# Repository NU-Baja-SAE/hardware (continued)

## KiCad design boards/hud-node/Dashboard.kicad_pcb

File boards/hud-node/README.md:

# hud-node

KiCad project for the HUD node board. Add `.kicad_pro`/`.kicad_sch`/`.kicad_pcb` files here, with generated fab outputs under `fab-outputs/` (gitignored).

<!-- CI trigger test -->

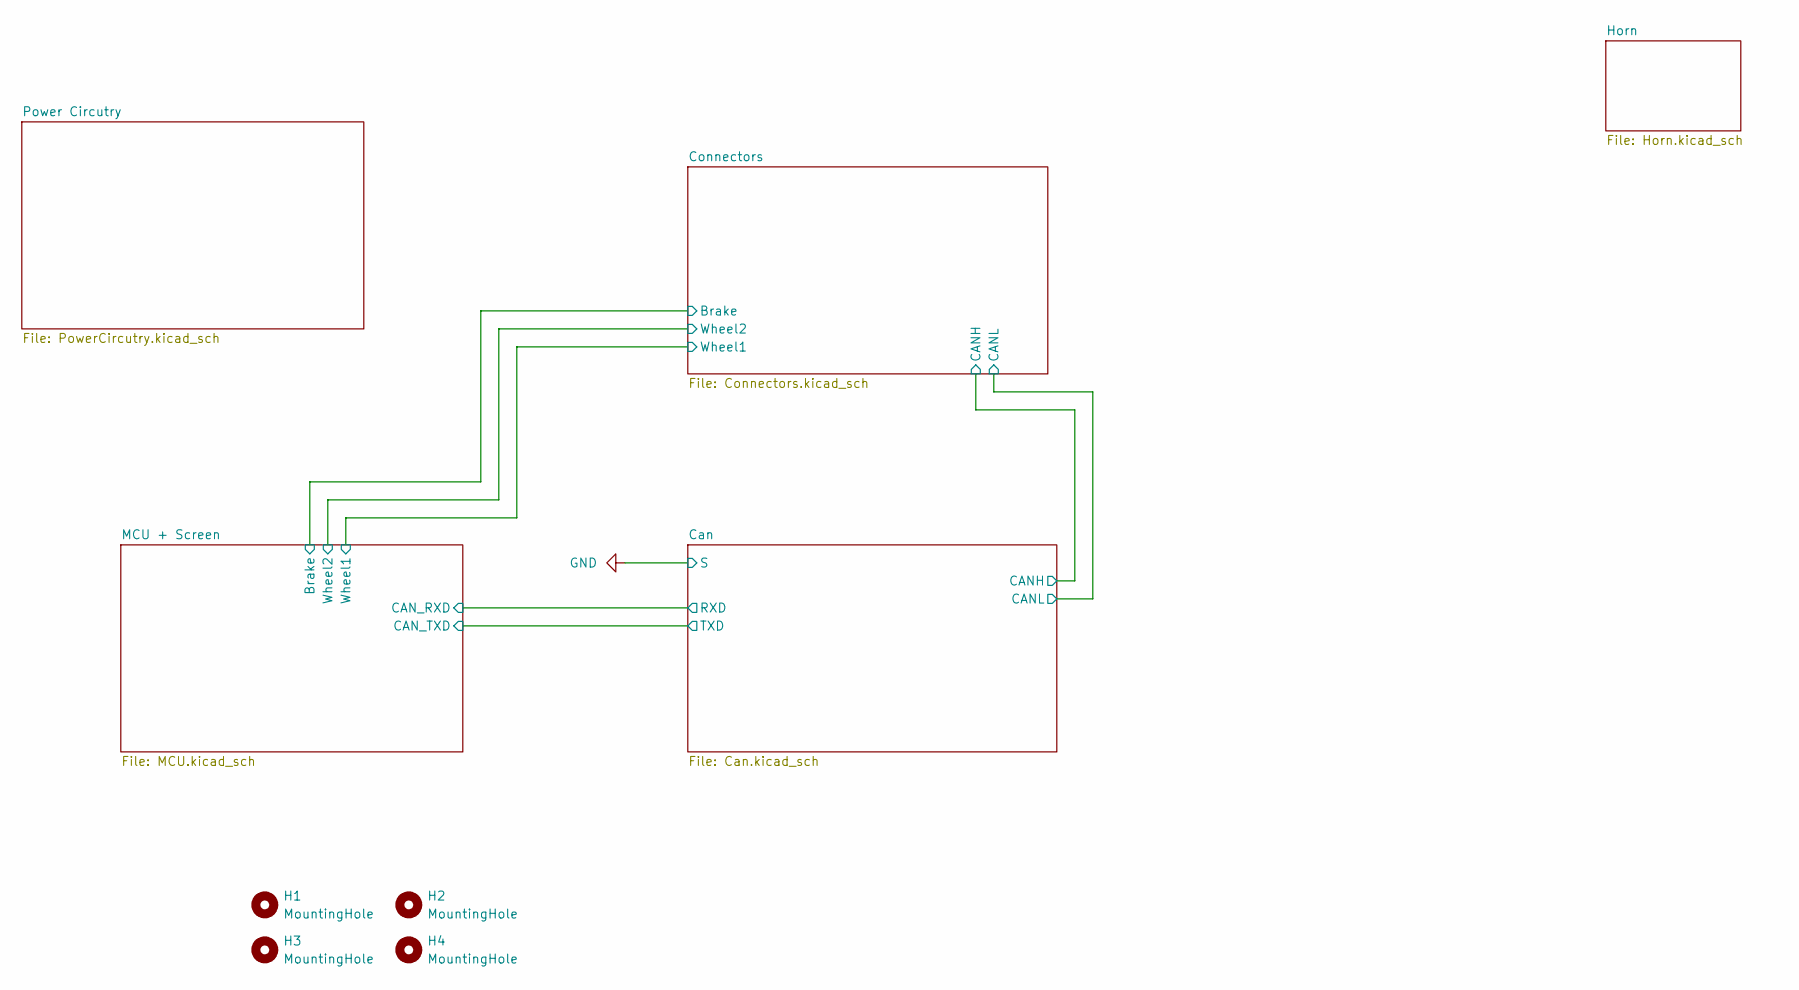
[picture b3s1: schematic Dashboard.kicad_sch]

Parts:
H1, H2, H3, H4: MountingHole; MountingHole_3.2mm_M3

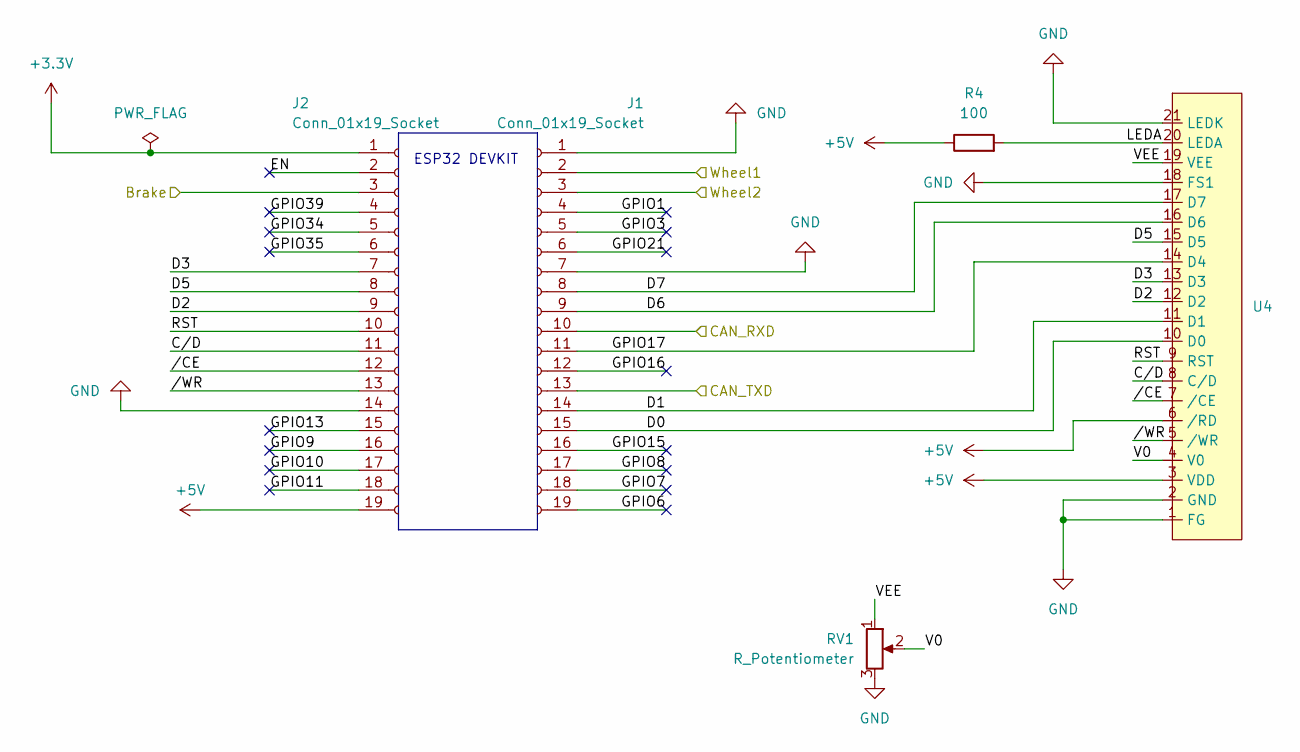
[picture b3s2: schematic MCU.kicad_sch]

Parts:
J1, J2: Conn_01x19_Socket; PinSocket_1x19_P2.54mm_Vertical
R4: 100; R_0603_1608Metric_Pad0.98x0.95mm_HandSolder
RV1: R_Potentiometer; Potentiometer_Bourns_3386F_Vertical
U4: PinHeader_1x21_P2.54mm_Vertical

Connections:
+3.3V: J2.1; also elsewhere on the board
+5V: J2.19, R4.1, U4.3 (VDD), U4.6 (/RD); also elsewhere on the board
/Can/RXD: J1.13; also elsewhere on the board
/Can/TXD: J1.10; also elsewhere on the board
/Connectors/Brake: J2.3; also elsewhere on the board
/Connectors/Wheel1: J1.2; also elsewhere on the board
/Connectors/Wheel2: J1.3; also elsewhere on the board
/MCU + Screen/C/D: J2.11, U4.8 (C/D)
/MCU + Screen/D0: J1.15, U4.10 (D0)
/MCU + Screen/D1: J1.14, U4.11 (D1)
/MCU + Screen/D3: J2.7, U4.13 (D3)
/MCU + Screen/D5: J2.8, U4.15 (D5)
/MCU + Screen/D6: J1.9, U4.16 (D6)
/MCU + Screen/D7: J1.8, U4.17 (D7)
/MCU + Screen/EN: J2.2
/MCU + Screen/GPIO1: J1.4
/MCU + Screen/GPIO3: J1.5
/MCU + Screen/GPIO6: J1.19
/MCU + Screen/GPIO7: J1.18
/MCU + Screen/GPIO8: J1.17
/MCU + Screen/GPIO9: J2.16
/MCU + Screen/GPIO10: J2.17
/MCU + Screen/GPIO11: J2.18
/MCU + Screen/GPIO13: J2.15
/MCU + Screen/GPIO15: J1.16
/MCU + Screen/GPIO16: J1.12
/MCU + Screen/GPIO17: J1.11, U4.14 (D4)
/MCU + Screen/GPIO21: J1.6
/MCU + Screen/GPIO34: J2.5
/MCU + Screen/GPIO39: J2.4
/MCU + Screen/LEDA: R4.2, U4.20 (LEDA)
/MCU + Screen/RST: J2.10, U4.9 (RST)
/MCU + Screen/V0: RV1.2, U4.4 (V0)
/MCU + Screen/VEE: RV1.1, U4.19 (VEE)
/MCU + Screen//CE: J2.12, U4.7 (/CE)
/MCU + Screen//WR: J2.13, U4.5 (/WR)
GND: J1.1, J1.7, J2.14, RV1.3, U4.1 (FG), U4.2 (GND), U4.18 (FS1), U4.21 (LEDK); also elsewhere on the board

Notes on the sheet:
ESP32 DEVKIT

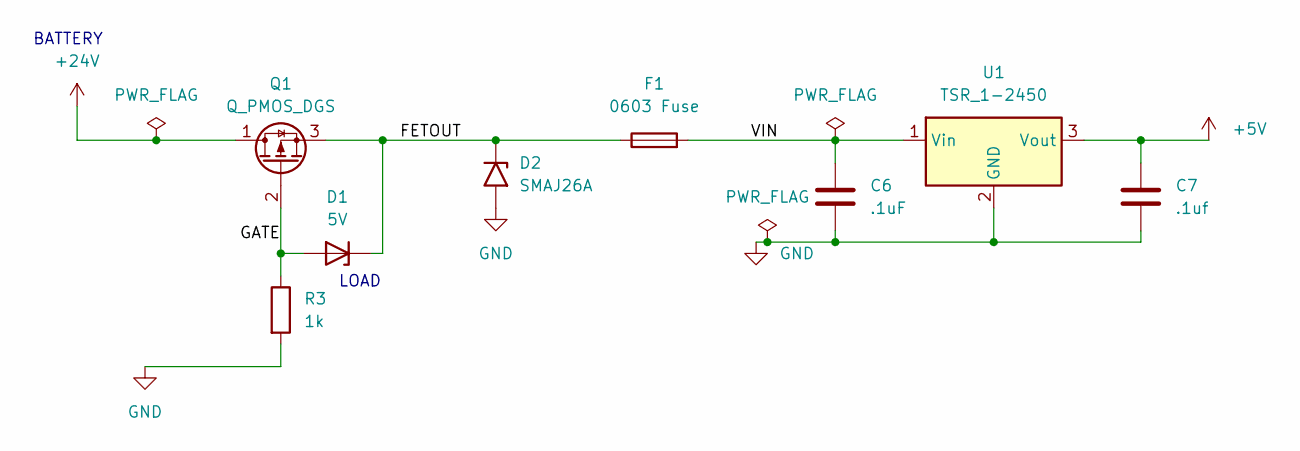
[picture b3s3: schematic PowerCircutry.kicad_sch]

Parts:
C6: .1uF; C_0603_1608Metric_Pad1.08x0.95mm_HandSolder
C7: .1uf; C_0805_2012Metric_Pad1.18x1.45mm_HandSolder
D1: 5V; D_SMA
D2: SMAJ26A; D_SMA
F1: 0603 Fuse; Fuse_0603_1608Metric_Pad1.05x0.95mm_HandSolder
Q1: Q_PMOS_DGS; SOT-23-3
R3: 1k; R_0603_1608Metric_Pad0.98x0.95mm_HandSolder
U1: TSR_1-2450; Converter_DCDC_TRACO_TSR-1_THT

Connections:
+5V: C7.1, U1.3 (Vout); also elsewhere on the board
+24V: Q1.1 (D); also elsewhere on the board
/Power Circutry/FETOUT: D1.1 (K), D2.1 (A1), F1.1, Q1.3 (S)
/Power Circutry/GATE: D1.2 (A), Q1.2 (G), R3.1
/Power Circutry/VIN: C6.1, F1.2, U1.1 (Vin)
GND: C6.2, C7.2, D2.2 (A2), R3.2, U1.2 (GND); also elsewhere on the board

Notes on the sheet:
LOAD
BATTERY

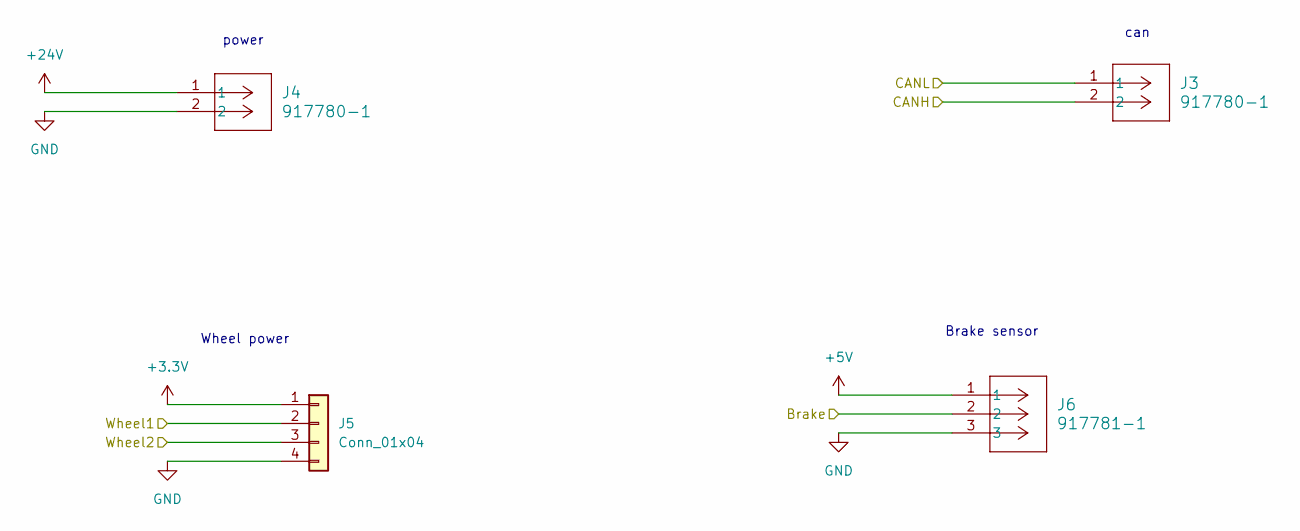
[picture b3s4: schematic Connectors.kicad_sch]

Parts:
J3, J4: 917780-1; TE-Connectivity_ 917780
J5: Conn_01x04; TE-Connectivity_917782
J6: 917781-1; TE-Connectivity_917781

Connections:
+3.3V: J5.1; also elsewhere on the board
+5V: J6.1; also elsewhere on the board
+24V: J4.1; also elsewhere on the board
/Can/CANH: J3.2; also elsewhere on the board
/Can/CANL: J3.1; also elsewhere on the board
/Connectors/Brake: J6.2; also elsewhere on the board
/Connectors/Wheel1: J5.2; also elsewhere on the board
/Connectors/Wheel2: J5.3; also elsewhere on the board
GND: J4.2, J5.4, J6.3; also elsewhere on the board

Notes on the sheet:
power
Brake sensor
Wheel power
can

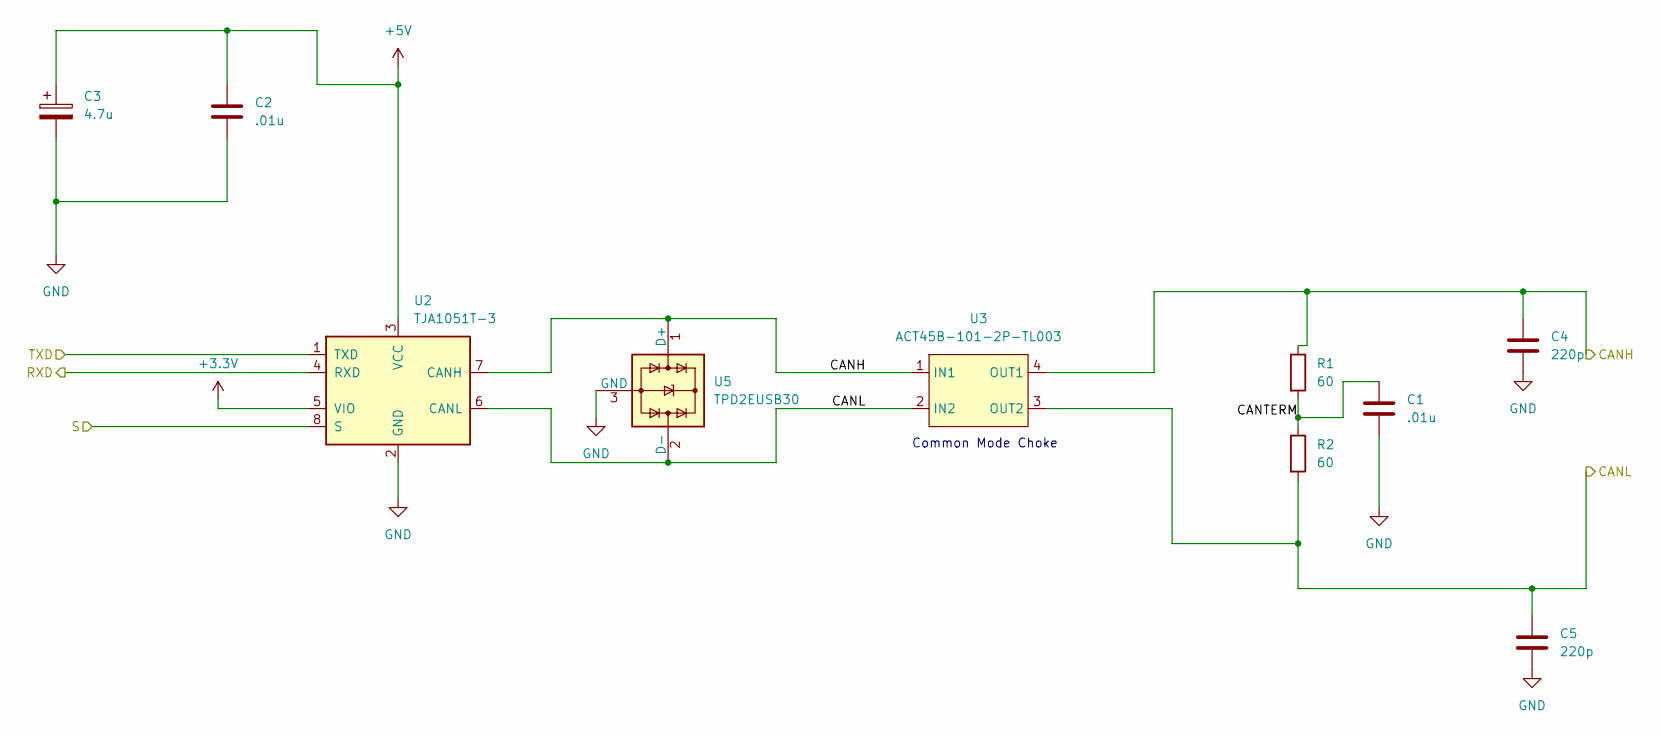
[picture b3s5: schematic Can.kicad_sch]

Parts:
C1, C2: .01u; C_0805_2012Metric_Pad1.18x1.45mm_HandSolder
C3: 4.7u; C_0603_1608Metric_Pad1.08x0.95mm_HandSolder
C4, C5: 220p; C_0603_1608Metric_Pad1.08x0.95mm_HandSolder
R1, R2: 60; R_1206_3216Metric_Pad1.30x1.75mm_HandSolder
U2: TJA1051T-3; SOIC-8_3.9x4.9mm_P1.27mm
U3: ACT45B-101-2P-TL003
U5: TPD2EUSB30; Texas_DRT-3

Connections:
+3.3V: U2.5 (VIO); also elsewhere on the board
+5V: C2.1, C3.1, U2.3 (VCC); also elsewhere on the board
/Can/CANH: C4.1, R1.1, U2.7 (CANH), U3.1 (IN1), U3.4 (OUT1), U5.1 (D+); also elsewhere on the board
/Can/CANL: C5.1, R2.2, U2.6 (CANL), U3.2 (IN2), U3.3 (OUT2), U5.2 (D-); also elsewhere on the board
/Can/CANTERM: C1.1, R1.2, R2.1
/Can/RXD: U2.4 (RXD); also elsewhere on the board
/Can/TXD: U2.1 (TXD); also elsewhere on the board
GND: C1.2, C2.2, C3.2, C4.2, C5.2, U2.2 (GND), U2.8 (S), U5.3 (GND); also elsewhere on the board

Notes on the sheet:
Common Mode Choke

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
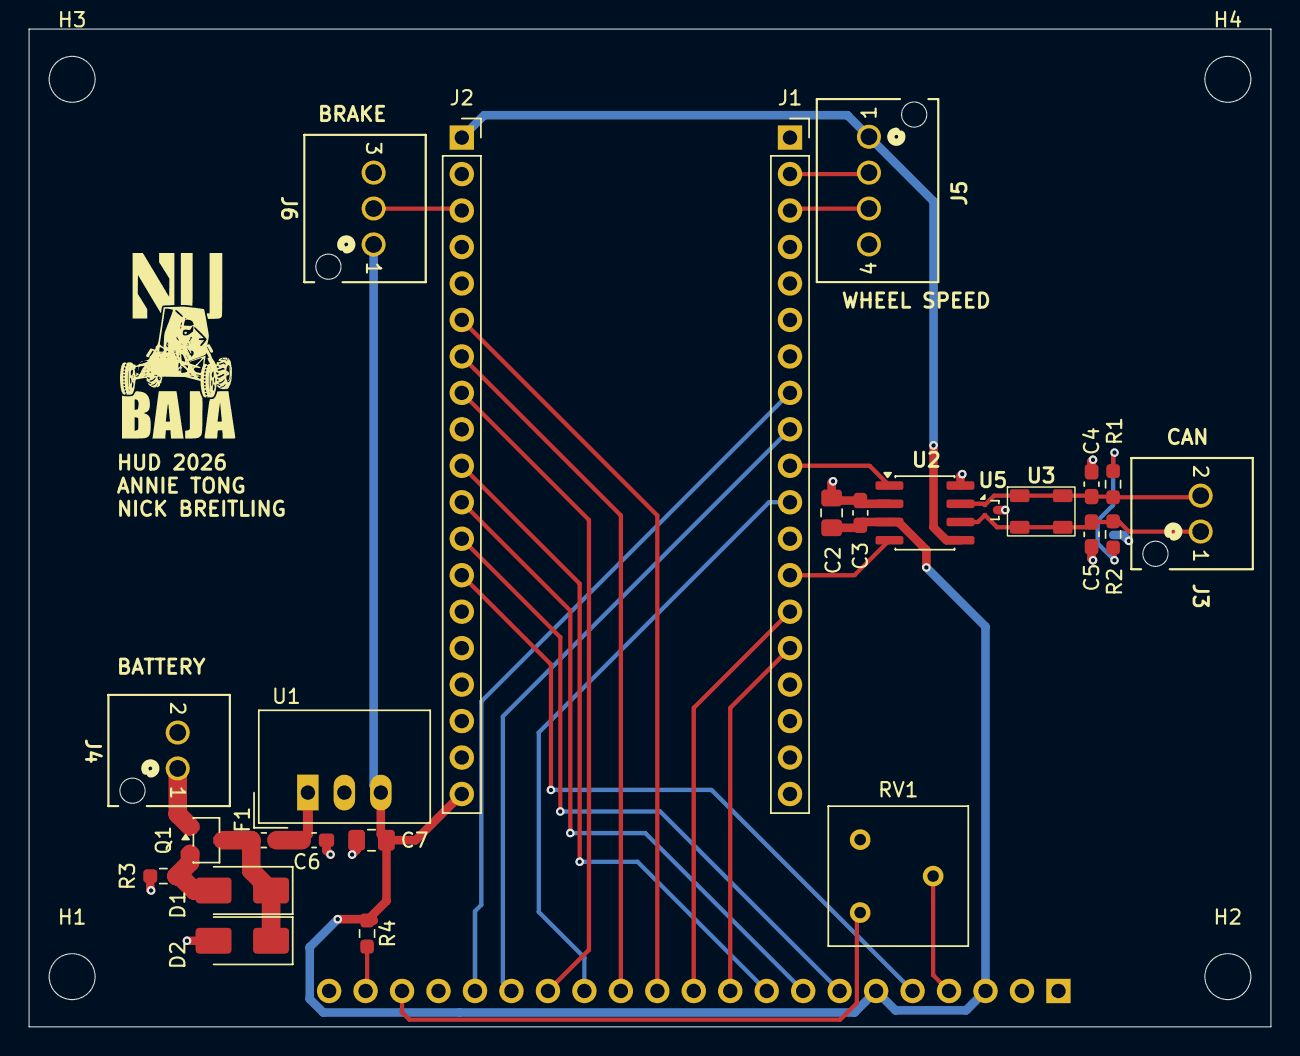
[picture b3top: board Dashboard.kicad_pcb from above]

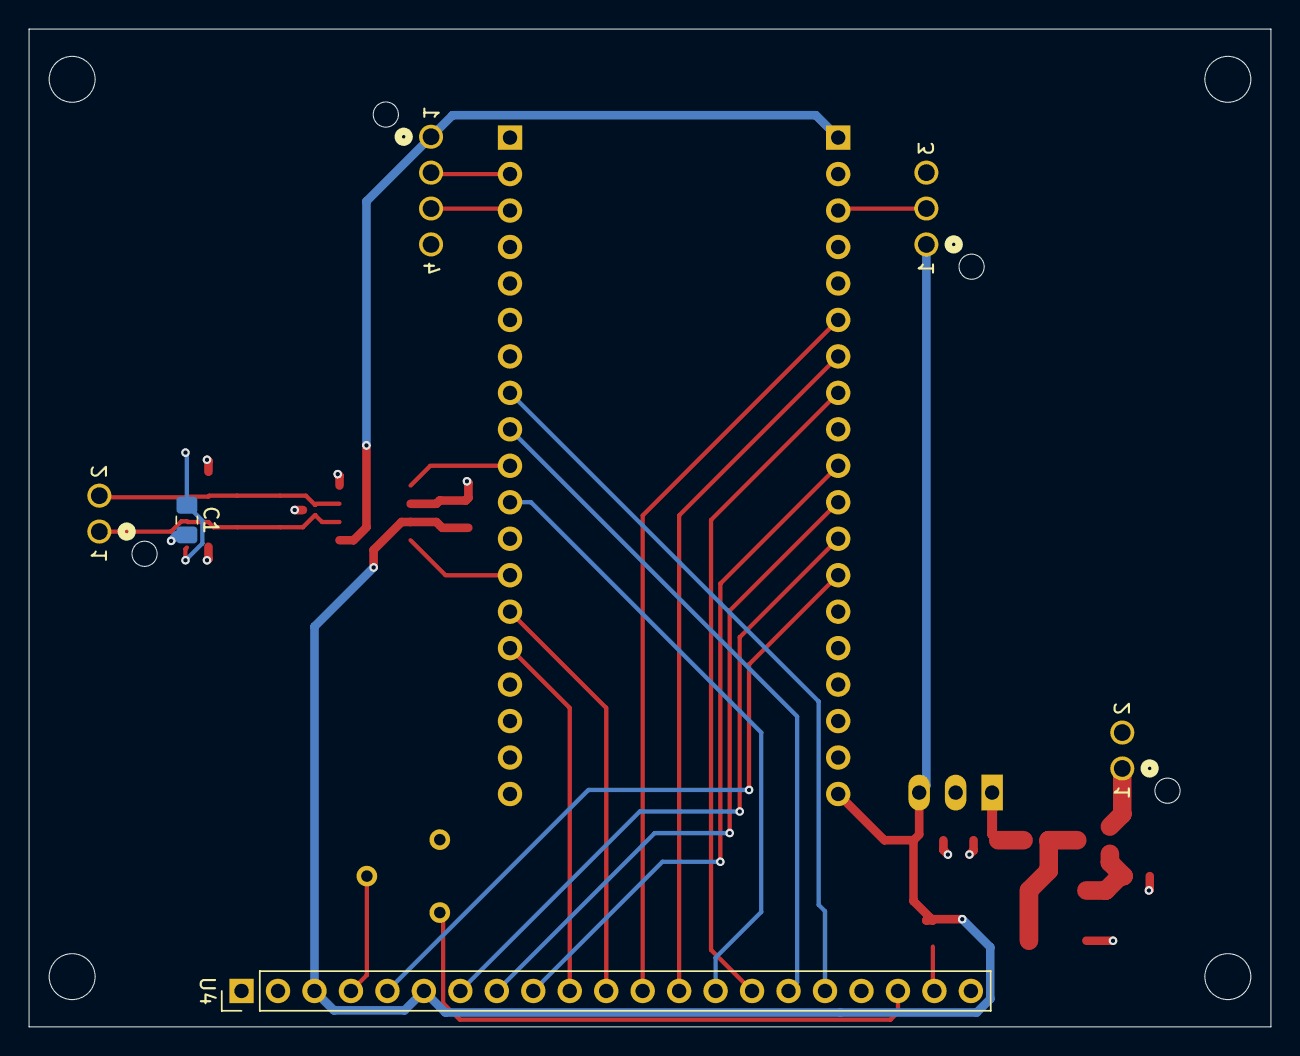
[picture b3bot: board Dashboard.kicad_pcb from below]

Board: 4 copper layers, 86.5 x 69.5 mm, 31 parts (2 on the bottom side), 30 nets.

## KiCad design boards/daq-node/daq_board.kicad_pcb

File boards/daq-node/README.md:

# daq-node

KiCad project for the DAQ node board. Add `.kicad_pro`/`.kicad_sch`/`.kicad_pcb` files here, with generated fab outputs under `fab-outputs/` (gitignored).

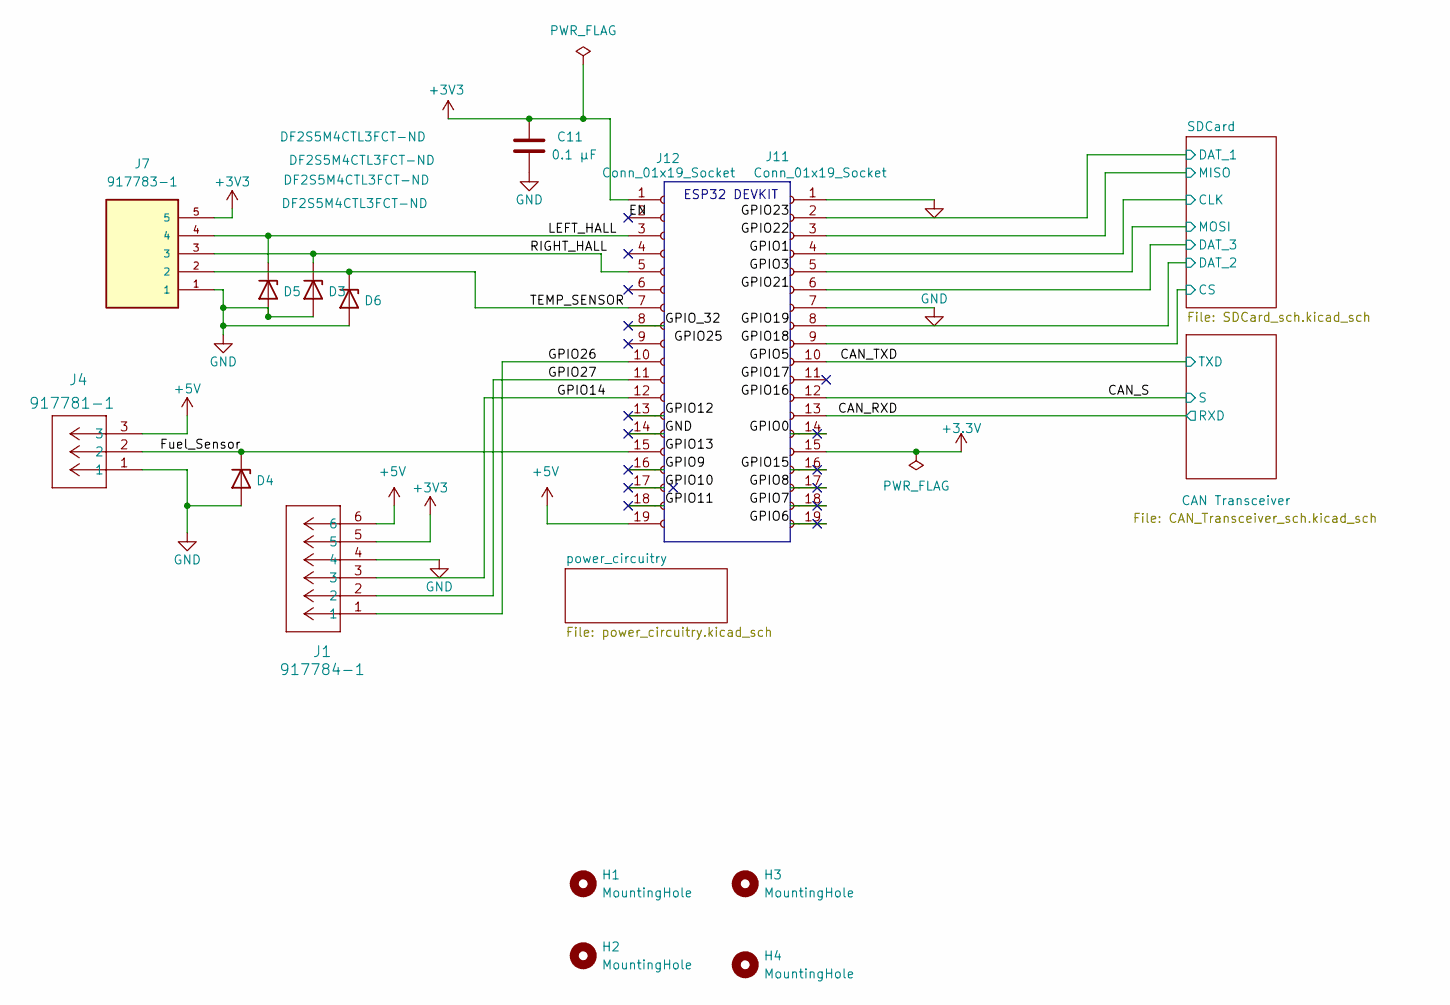
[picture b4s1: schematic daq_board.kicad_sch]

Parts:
C11: 0.1 µF; C_0603_1608Metric_Pad1.08x0.95mm_HandSolder
D3, D4, D5, D6: DF2S5M4CTL3FCT-ND; D_SOD-882
H1, H2, H3, H4: MountingHole; MountingHole_3.2mm_M3
J1: 917784-1; TE-Connectivity_1x6
J4: 917781-1; CON3_1X3_P100
J7: 917783-1; Connector_1x5; PARTREV R
J11, J12: Conn_01x19_Socket; PinSocket_1x19_P2.54mm_Vertical

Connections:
+3.3V: J11.15; also elsewhere on the board
+3V3: C11.1, J1.5, J7.5, J12.1; also elsewhere on the board
+5V: J1.6, J4.3, J12.19; also elsewhere on the board
/CAN_RXD: J11.13; also elsewhere on the board
/CAN_S: J11.12; also elsewhere on the board
/CAN_TXD: J11.10; also elsewhere on the board
/EN: J12.2
/Fuel_Sensor: D4.1 (K), J4.2, J12.15
/GPIO0: J11.14
/GPIO6: J11.19
/GPIO7: J11.18
/GPIO8: J11.17
/GPIO9: J12.16
/GPIO10: J12.17
/GPIO11: J12.18
/GPIO12: J12.13
/GPIO14: J1.3, J12.12
/GPIO15: J11.16
/GPIO26: J1.1, J12.10
/GPIO27: J1.2, J12.11
/GPIO_32: J12.8
/LEFT_HALL: D5.1 (K), J7.4, J12.3
/RIGHT_HALL: D3.1 (K), J7.3, J12.5
/SDCard/CLK: J11.4; also elsewhere on the board
/SDCard/CS: J11.9; also elsewhere on the board
/SDCard/DAT_1: J11.2; also elsewhere on the board
/SDCard/DAT_2: J11.8; also elsewhere on the board
/SDCard/DAT_3: J11.6; also elsewhere on the board
/SDCard/MISO: J11.3; also elsewhere on the board
/SDCard/MOSI: J11.5; also elsewhere on the board
/TEMP_SENSOR: D6.1 (K), J7.2, J12.7
GND: C11.2, D3.2 (A), D4.2 (A), D5.2 (A), D6.2 (A), J1.4, J4.1, J7.1, J11.1, J11.7, J12.14; also elsewhere on the board

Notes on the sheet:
ESP32 DEVKIT

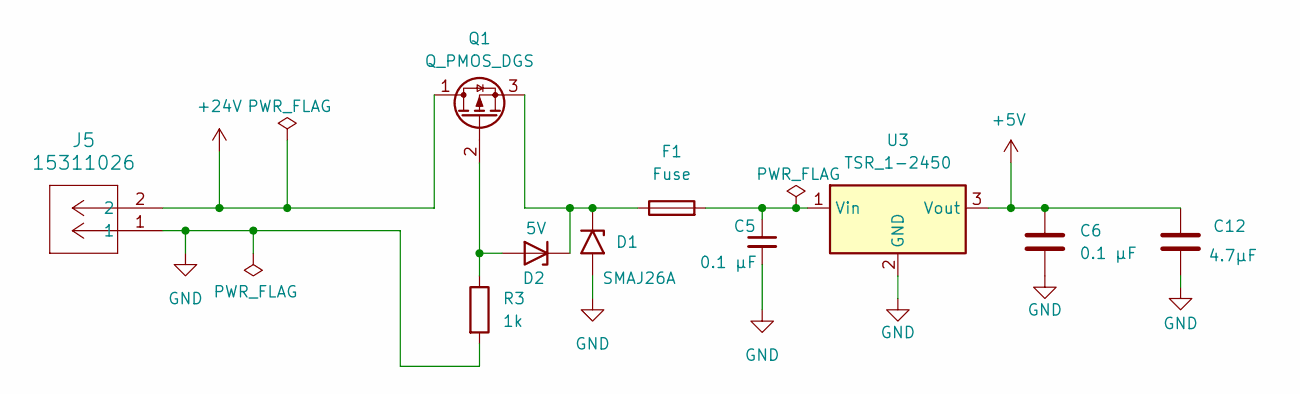
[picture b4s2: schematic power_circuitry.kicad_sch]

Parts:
C5: 0.1 µF; C_0603_1608Metric_Pad1.08x0.95mm_HandSolder
C6: 0.1 µF; C_0805_2012Metric_Pad1.18x1.45mm_HandSolder
C12: 4.7µF; C_0603_1608Metric_Pad1.08x0.95mm_HandSolder
D1: SMAJ26A; D_SMA
D2: 5V; D_SMA
F1: Fuse; Fuse_0603_1608Metric_Pad1.05x0.95mm_HandSolder
J5: 15311026; MOLEX_15311026
Q1: Q_PMOS_DGS; SOT-23-3
R3: 1k; R_0603_1608Metric_Pad0.98x0.95mm_HandSolder
U3: TSR_1-2450; Converter_DCDC_TRACO_TSR-1_THT

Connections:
+5V: C6.1, C12.1, U3.3 (Vout); also elsewhere on the board
+24V: J5.2, Q1.1 (D)
GND: C5.2, C6.2, C12.2, D1.2 (A2), J5.1, R3.2, U3.2 (GND); also elsewhere on the board
unnamed: D1.1 (A1), D2.1 (K), F1.1, Q1.3 (S)
unnamed: D2.2 (A), Q1.2 (G), R3.1
unnamed: C5.1, F1.2, U3.1 (Vin)

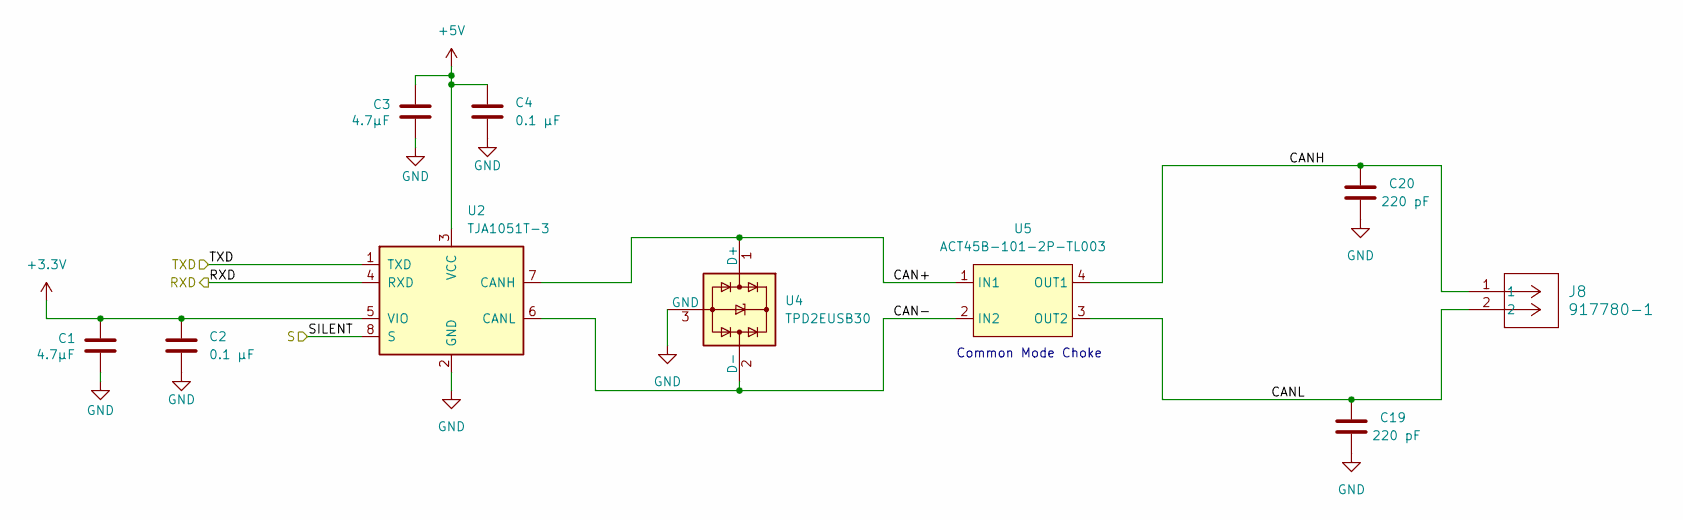
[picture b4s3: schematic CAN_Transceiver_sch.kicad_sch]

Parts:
C1, C3: 4.7µF; C_0603_1608Metric_Pad1.08x0.95mm_HandSolder
C2, C4: 0.1 µF; C_0805_2012Metric_Pad1.18x1.45mm_HandSolder
C19, C20: 220 pF; C_0603_1608Metric_Pad1.08x0.95mm_HandSolder
J8: 917780-1; CON2_1X2_P100
U2: TJA1051T-3; SOIC-8_3.9x4.9mm_P1.27mm
U4: TPD2EUSB30; Texas_DRT-3
U5: ACT45B-101-2P-TL003

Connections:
+3.3V: C1.1, C2.1, U2.5 (VIO); also elsewhere on the board
+5V: C3.1, C4.1, U2.3 (VCC); also elsewhere on the board
/CAN Transceiver/CAN+: U2.7 (CANH), U4.1 (D+), U5.1 (IN1)
/CAN Transceiver/CAN-: U2.6 (CANL), U4.2 (D-), U5.2 (IN2)
/CAN Transceiver/CANH: C20.1, J8.1, U5.4 (OUT1)
/CAN Transceiver/CANL: C19.1, J8.2, U5.3 (OUT2)
/CAN_RXD: U2.4 (RXD); also elsewhere on the board
/CAN_S: U2.8 (S); also elsewhere on the board
/CAN_TXD: U2.1 (TXD); also elsewhere on the board
GND: C1.2, C2.2, C3.2, C4.2, C19.2, C20.2, U2.2 (GND), U4.3 (GND); also elsewhere on the board

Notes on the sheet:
Common Mode Choke

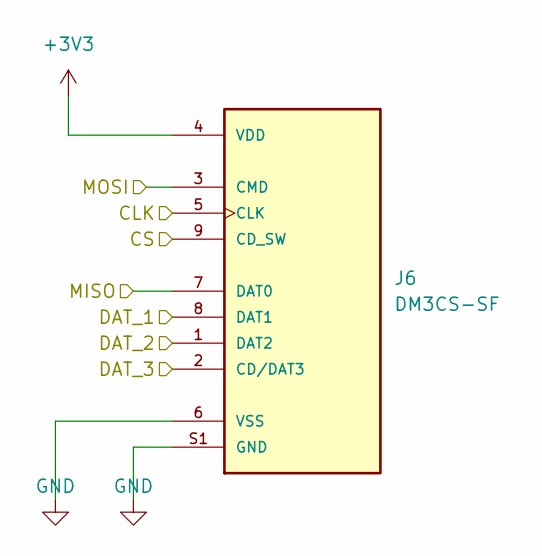
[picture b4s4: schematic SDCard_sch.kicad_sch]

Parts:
J6: DM3CS-SF; SD_Card; PARTREV n/a

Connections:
+3V3: J6.4 (VDD); also elsewhere on the board
/SDCard/CLK: J6.5 (CLK); also elsewhere on the board
/SDCard/CS: J6.9 (CD_SW); also elsewhere on the board
/SDCard/DAT_1: J6.8 (DAT1); also elsewhere on the board
/SDCard/DAT_2: J6.1 (DAT2); also elsewhere on the board
/SDCard/DAT_3: J6.2 (CD/DAT3); also elsewhere on the board
/SDCard/MISO: J6.7 (DAT0); also elsewhere on the board
/SDCard/MOSI: J6.3 (CMD); also elsewhere on the board
GND: J6.6 (VSS), J6.S1 (GND), J6.S2 (GND), J6.S3 (GND), J6.S5 (GND); also elsewhere on the board

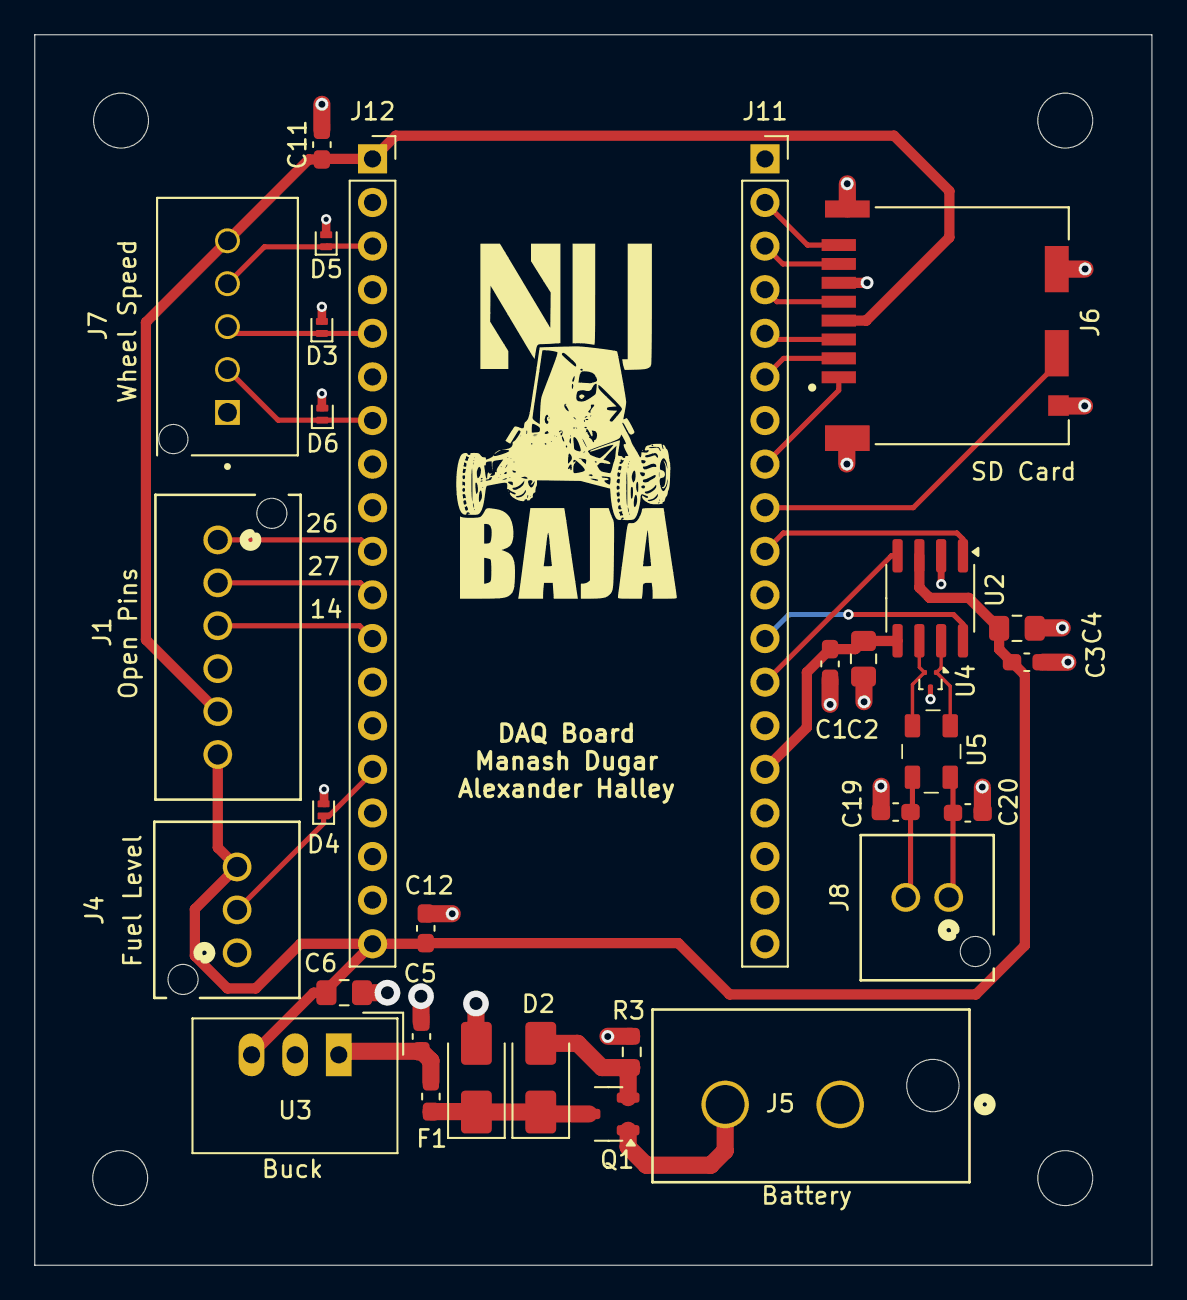
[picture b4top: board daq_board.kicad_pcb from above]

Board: 2 copper layers, 65.1 x 71.7 mm, 35 parts (0 on the bottom side), 29 nets.

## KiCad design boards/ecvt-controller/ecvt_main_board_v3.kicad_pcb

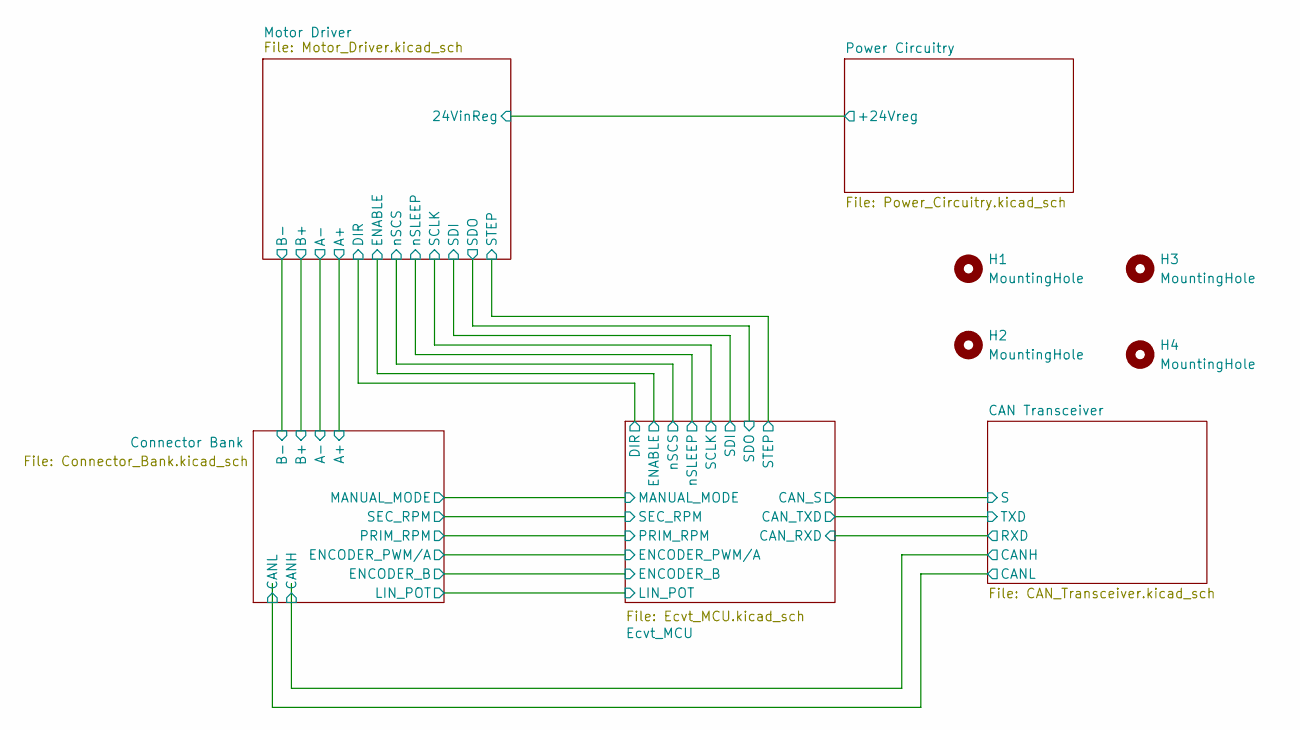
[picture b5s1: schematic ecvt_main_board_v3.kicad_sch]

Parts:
H1, H2, H3, H4: MountingHole; MountingHole_3.2mm_M3

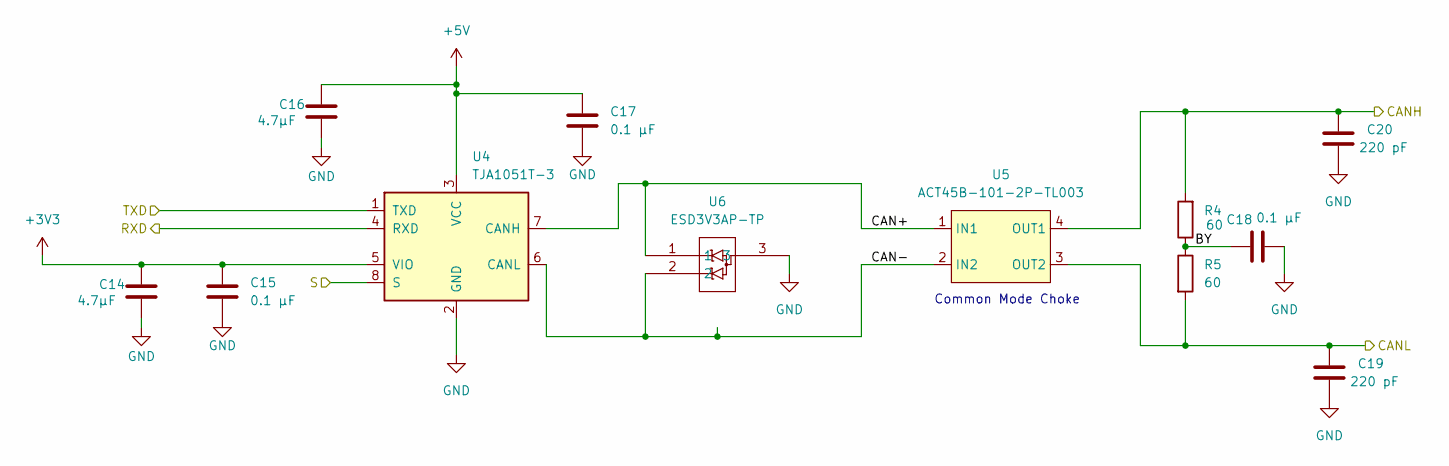
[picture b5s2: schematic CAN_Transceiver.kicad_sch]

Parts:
C14, C16: 4.7µF; C_0603_1608Metric_Pad1.08x0.95mm_HandSolder
C15, C17, C18: 0.1 µF; C_0603_1608Metric_Pad1.08x0.95mm_HandSolder
C19, C20: 220 pF; C_0603_1608Metric_Pad1.08x0.95mm_HandSolder
R4, R5: 60; R_1206_3216Metric_Pad1.30x1.75mm_HandSolder
U4: TJA1051T-3; SOIC-8_3.9x4.9mm_P1.27mm
U5: ACT45B-101-2P-TL003
U6: ESD3V3AP-TP; SOT-23

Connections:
+3V3: C14.1, C15.1, U4.5 (VIO); also elsewhere on the board
+5V: C16.1, C17.1, U4.3 (VCC); also elsewhere on the board
/CAN Transceiver/BY: C18.1, R4.1, R5.1
/CAN Transceiver/CAN+: U4.7 (CANH), U5.1 (IN1), U6.1
/CAN Transceiver/CAN-: U4.6 (CANL), U5.2 (IN2), U6.2
/CAN Transceiver/CANH: C20.1, R4.2, U5.4 (OUT1); also elsewhere on the board
/CAN Transceiver/CANL: C19.1, R5.2, U5.3 (OUT2); also elsewhere on the board
/CAN Transceiver/RXD: U4.4 (RXD); also elsewhere on the board
/CAN Transceiver/S: U4.8 (S); also elsewhere on the board
/CAN Transceiver/TXD: U4.1 (TXD); also elsewhere on the board
GND: C14.2, C15.2, C16.2, C17.2, C18.2, C19.2, C20.2, U4.2 (GND), U6.3; also elsewhere on the board

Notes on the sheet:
Common Mode Choke

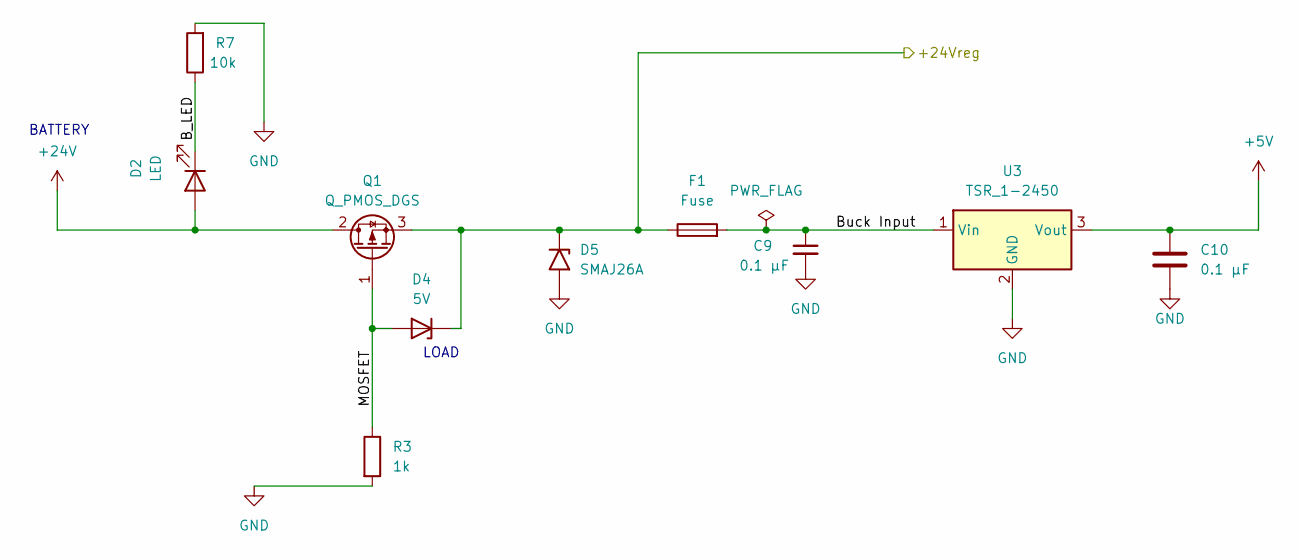
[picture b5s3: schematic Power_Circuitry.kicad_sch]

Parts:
C9, C10: 0.1 µF; C_0603_1608Metric_Pad1.08x0.95mm_HandSolder
D2: LED; LED_Luminus_MP-3030-1100_3.0x3.0mm
D4: 5V; D_SMA
D5: SMAJ26A; D_SMA
F1: Fuse; Fuse_0603_1608Metric_Pad1.05x0.95mm_HandSolder
Q1: Q_PMOS_DGS; SOT-23-3
R3: 1k; R_0603_1608Metric_Pad0.98x0.95mm_HandSolder
R7: 10k; R_0603_1608Metric_Pad0.98x0.95mm_HandSolder
U3: TSR_1-2450; Converter_DCDC_TRACO_TSR-1_THT

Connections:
+5V: C10.1, U3.3 (Vout); also elsewhere on the board
+24V: D2.2 (A), Q1.2 (D); also elsewhere on the board
/Motor Driver/24VinReg: D4.1 (K), D5.1 (A1), F1.1, Q1.3 (S); also elsewhere on the board
/Power Circuitry/B_LED: D2.1 (K), R7.1
/Power Circuitry/Buck Input: C9.1, F1.2, U3.1 (Vin)
/Power Circuitry/MOSFET: D4.2 (A), Q1.1 (G), R3.1
GND: C9.2, C10.2, D5.2 (A2), R3.2, R7.2, U3.2 (GND); also elsewhere on the board

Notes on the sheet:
BATTERY
LOAD
